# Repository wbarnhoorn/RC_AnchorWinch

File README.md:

# RC Anchor Winch
A free fall anchorwinch controlled by a single RC channel

This is an anchor winch for scale model ships.
Controlled by a single RC channel using a PWM pulse of >1800ms

Control board designed with KiCAD  
Based on an Arduino Nano

Uses a servo to attach and detach a winchmotor to the winchdrum.  
Actual physical design is up to the builder.

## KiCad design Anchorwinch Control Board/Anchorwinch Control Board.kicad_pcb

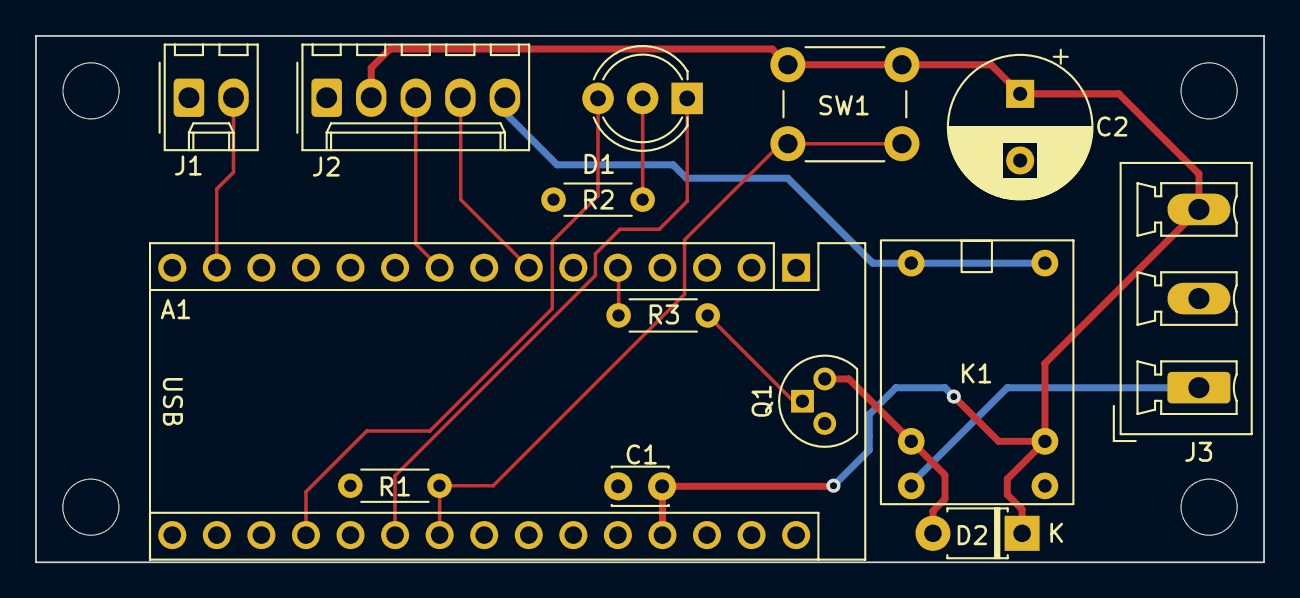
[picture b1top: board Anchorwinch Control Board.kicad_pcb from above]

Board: 2 copper layers, 70.0 x 30.0 mm, 14 parts (0 on the bottom side), 14 nets.

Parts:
A1: Arduino_Nano_v2.x; Arduino_Nano
C1: 10nF; C_Disc_D3.0mm_W2.0mm_P2.50mm
C2: 470µF; CP_Radial_D8.0mm_P3.80mm
D1: Red/Green; LED_D5.0mm-3
D2: 1N4007; D_T-1_P5.08mm_Horizontal
J1: Molex; Molex_KK-254_AE-6410-02A_1x02_P2.54mm_Vertical
J2: Molex; Molex_KK-254_AE-6410-05A_1x05_P2.54mm_Vertical
J3: Screw Terminal; PhoenixContact_MCV_1,5_3-G-5.08_1x03_P5.08mm_Vertical
K1: JRC-21F
Q1: 2N3904; TO-92
R1: 10K; R_Axial_DIN0204_L3.6mm_D1.6mm_P5.08mm_Horizontal
R2, R3: 1K; R_Axial_DIN0204_L3.6mm_D1.6mm_P5.08mm_Horizontal
SW1: SW_Push; SW_PUSH_6mm

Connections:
+3V0: J3.1, K1.3
+5V: A1.27 (+5V), C1.1, C2.1, D2.1 (K), J2.2, J3.3, K1.5, SW1.1
GND: A1.4 (GND), A1.29 (GND), C1.2, C2.2, J1.1, J2.1, J3.2, Q1.3 (E), R1.2, R2.1
unnamed: A1.5 (D2), R3.1
unnamed: A1.7 (D4), J2.4
unnamed: A1.9 (D6), J2.3
unnamed: A1.14 (D11), J1.2
unnamed: A1.19 (A0), D1.2 (A2)
unnamed: A1.21 (A2), D1.1 (A1)
unnamed: A1.22 (A3), R1.1, SW1.2
unnamed: D1.3 (K), R2.2
unnamed: D2.2 (A), K1.2, Q1.2 (C)
unnamed: J2.5, K1.1, K1.6
unnamed: Q1.1 (B), R3.2

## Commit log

2023-04-11 Comment
